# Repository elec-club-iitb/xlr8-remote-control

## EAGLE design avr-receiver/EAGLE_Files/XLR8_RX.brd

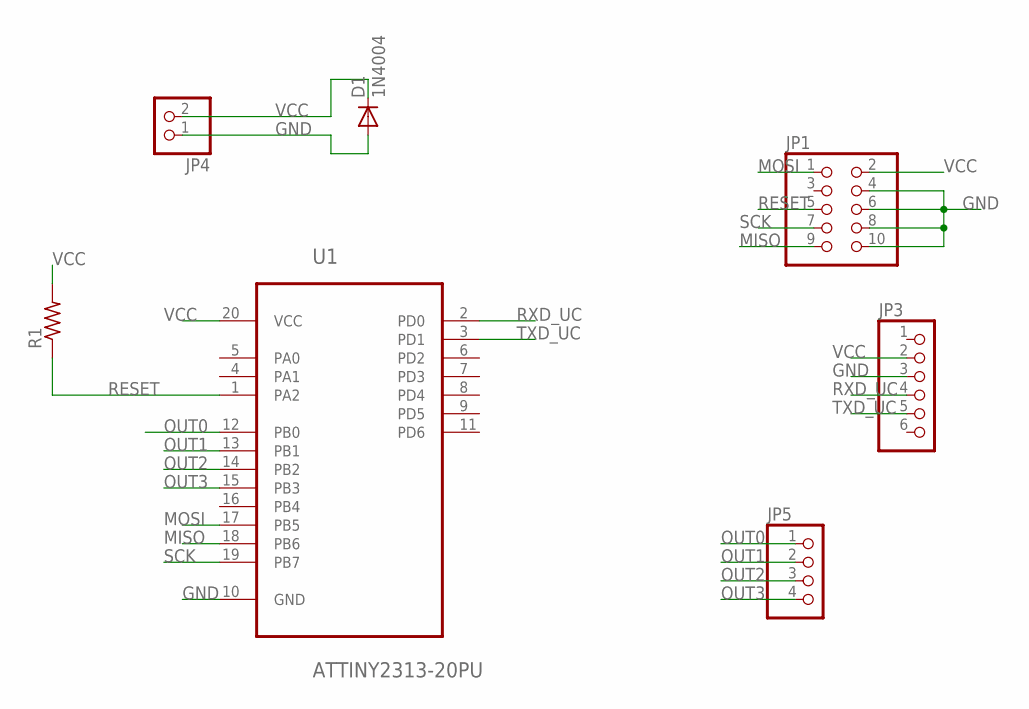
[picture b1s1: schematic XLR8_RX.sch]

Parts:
D1: 1N4004; DO41-10
JP1: PINHD-2X5; 2X05
JP3: PINHD-1X6; 1X06
JP4: PINHD-1X2; 1X02
JP5: PINHD-1X4; 1X04
R1: R-US_0207/10; 0207/10
U1: ATTINY2313-20PU; DIP254P762X533-20

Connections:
GND: D1.A, JP1.4, JP1.6, JP1.8, JP1.10, JP3.3, JP4.1, U1.10 (GND)
MISO: JP1.9, U1.18 (PB6)
MOSI: JP1.1, U1.17 (PB5)
OUT0: JP5.1, U1.12 (PB0)
OUT1: JP5.2, U1.13 (PB1)
OUT2: JP5.3, U1.14 (PB2)
OUT3: JP5.4, U1.15 (PB3)
RESET: JP1.5, R1.1, U1.1 (PA2)
RXD_UC: JP3.4, U1.2 (PD0)
SCK: JP1.7, U1.19 (PB7)
TXD_UC: JP3.5, U1.3 (PD1)
VCC: D1.C, JP1.2, JP3.2, JP4.2, R1.2, U1.20 (VCC)

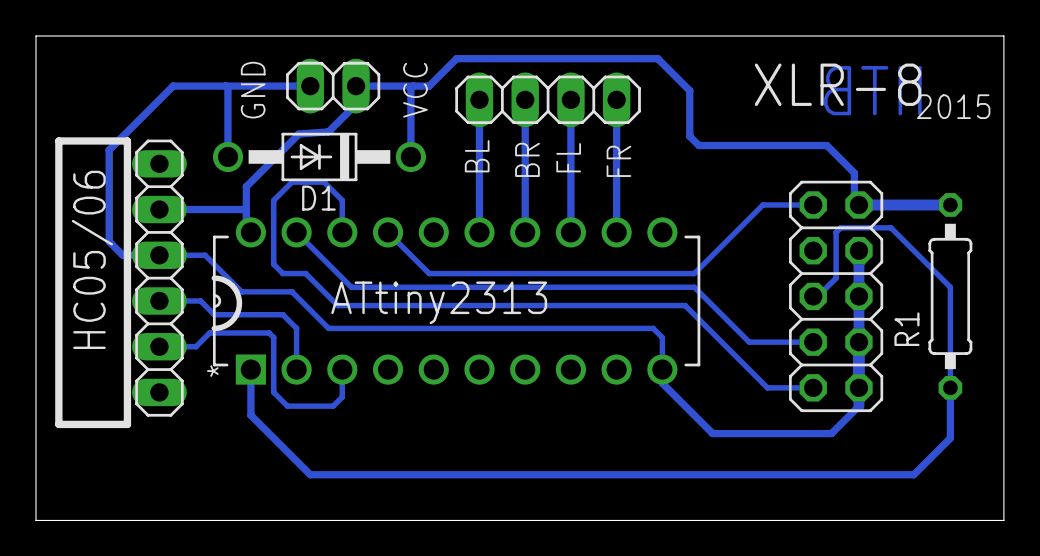
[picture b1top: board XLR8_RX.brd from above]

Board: 2 copper layers, 53.8 x 26.9 mm, 7 parts (0 on the bottom side), 12 nets.

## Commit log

2015-08-21 Swag BC
2015-08-21 Remove test feature code (cherry picked from commit def76b7)
2015-08-21 Add comments
2015-08-21 Add comments for swag mode
2016-03-04 Add AVR receiver module and restructure dir tree
2016-03-04 Update gitignores
2016-08-17 Change package name and build settings
2017-08-30 Bugfixes and Logo change
2017-09-02 Change FCK=8MHz
